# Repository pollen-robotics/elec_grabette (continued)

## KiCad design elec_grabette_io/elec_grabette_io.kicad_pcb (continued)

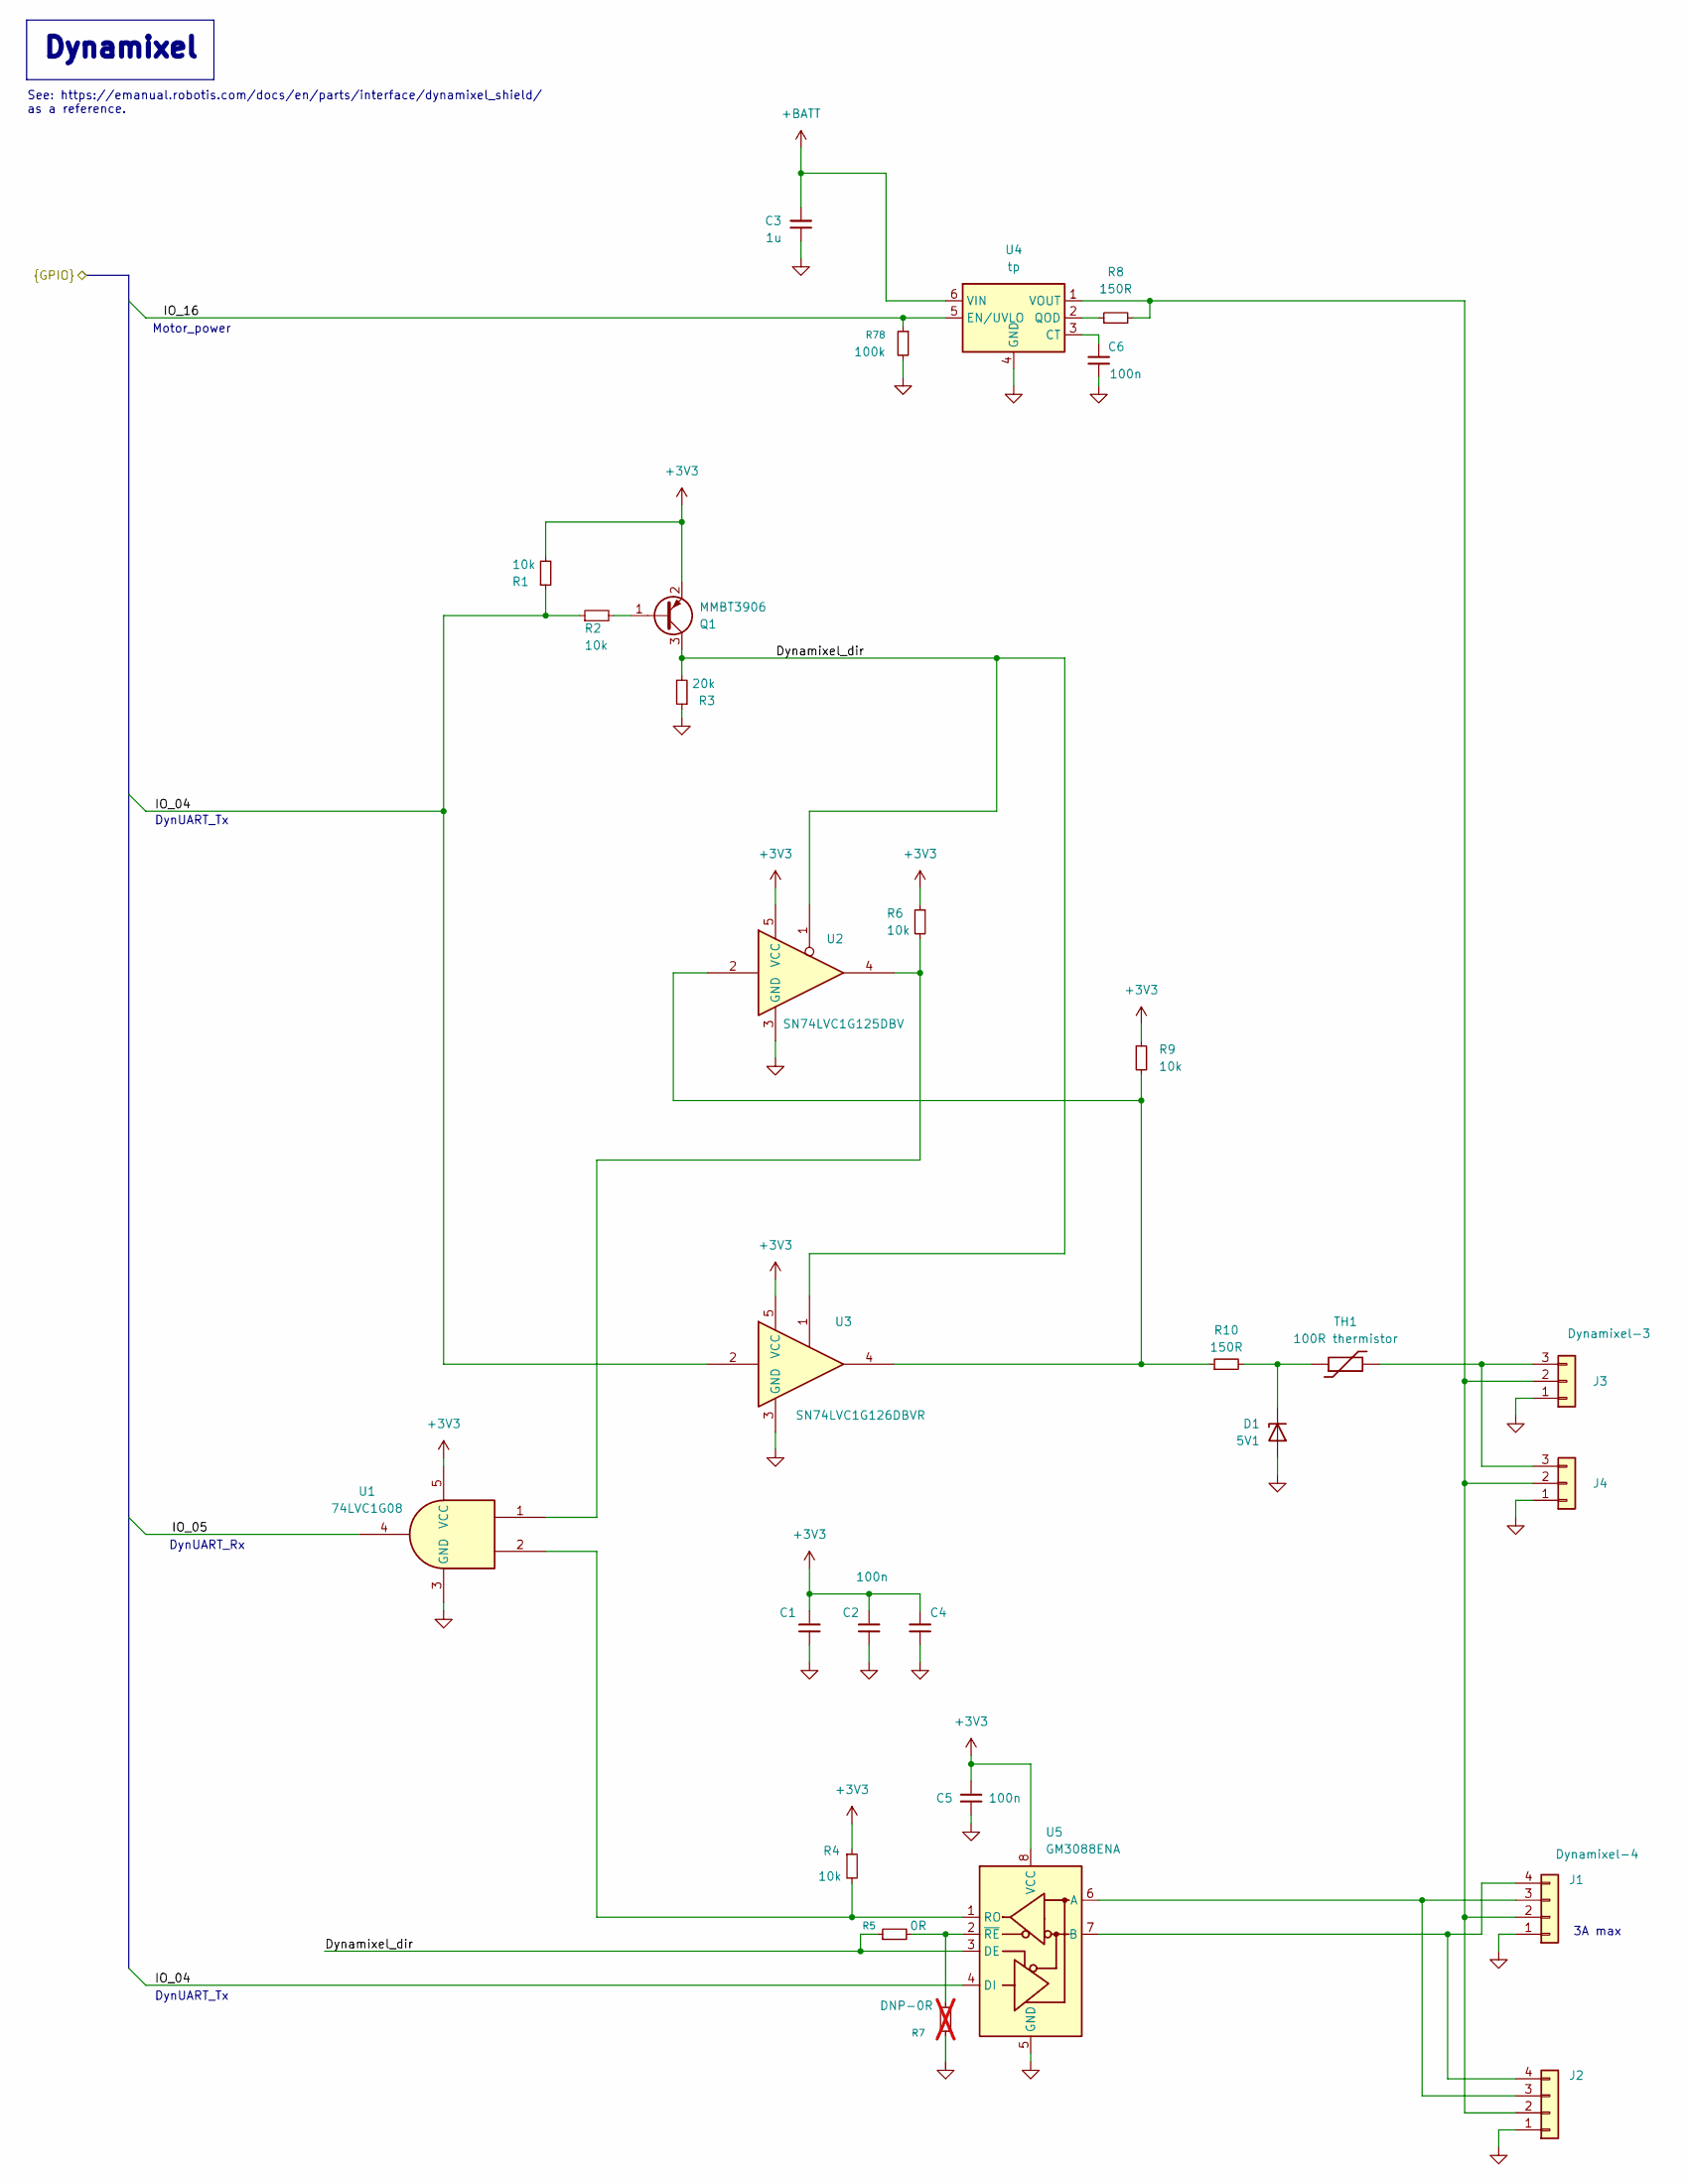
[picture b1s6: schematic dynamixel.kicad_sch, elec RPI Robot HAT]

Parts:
C1, C2, C4, C5, C6: 100n; C_0402_1005Metric; LCSC Part C307331
C3: 1u; C_0402_1005Metric; LCSC Part C52923
D1: 5V1; D_SOD-323; LCSC Part C151348
J1, J2: Dynamixel-4; JST_EH_B4B-EH-A_1x04_P2.50mm_Vertical; LCSC Part C160258
J3, J4: Dynamixel-3; JST_EH_B3B-EH-A_1x03_P2.50mm_Vertical; LCSC Part C160259
Q1: MMBT3906; SOT-23; LCSC Part C727128
R1, R2, R4, R6, R9: 10k; R_0402_1005Metric; LCSC Part C25744
R3: 20k; R_0402_1005Metric; LCSC Part C25765
R5: 0R; R_0402_1005Metric; LCSC Part C17168
R7: DNP-0R; R_0402_1005Metric; not fitted
R8, R10: 150R; R_0402_1005Metric; LCSC Part C2909321
R78: 100k; R_0402_1005Metric; LCSC Part C22369186
TH1: 100R thermistor; R_0603_1608Metric; LCSC Part C913703
U1: 74LVC1G08; SOT-23-5; LCSC Part C7666
U2: SN74LVC1G125DBV; SOT-23-5; LCSC Part C23654
U3: SN74LVC1G126DBVR; SOT-23-5; LCSC Part C7834
U4: tp; WSON-6-1EP_2x2mm_P0.65mm_EP1x1.6mm; LCSC Part C527679
U5: GM3088ENA; DFN-8-1EP_3x3mm_P0.65mm_EP1.2x2.15mm; LCSC Part C49423279

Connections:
+3V3: C1.2, C2.2, C4.2, C5.2, Q1.2 (E), R1.2, R4.1, R6.1, R9.1, U1.5 (VCC), U2.5 (VCC), U3.5 (VCC), U5.8 (VCC); also elsewhere on the board
+BATT: C3.2, U4.6 (VIN); also elsewhere on the board
/Audio/IO_04: R1.1, R2.1, U3.2, U5.4 (DI); also elsewhere on the board
/Audio/IO_05: U1.4; also elsewhere on the board
/Audio/IO_16: R78.1, U4.5 (EN/UVLO); also elsewhere on the board
/Dynamixel/Dynamixel_dir: Q1.3 (C), R3.2, R5.1, U2.1, U3.1, U5.3 (DE)
GND: C1.1, C2.1, C3.1, C4.1, C5.1, C6.1, D1.2 (A), J1.1, J2.1, J3.1, J4.1, R3.1, R7.1, R78.2, U1.3 (GND), U2.3 (GND), U3.3 (GND), U4.4 (GND), U4.7 (GND), U5.5 (GND); also elsewhere on the board
unnamed: D1.1 (K), R10.2, TH1.1
unnamed: J1.2, J2.2, J3.2, J4.2, R8.2, U4.1 (VOUT)
unnamed: J1.3, J2.3, U5.6 (A)
unnamed: J1.4, J2.4, U5.7 (B)
unnamed: J3.3, J4.3, TH1.2
unnamed: Q1.1 (B), R2.2
unnamed: R6.2, U1.1, U2.4
unnamed: R9.2, R10.1, U2.2, U3.4
unnamed: C6.2, U4.3 (CT)
unnamed: R8.1, U4.2 (QOD)
unnamed: R4.2, U1.2, U5.1 (RO)
unnamed: R5.2, R7.2, U5.2 (~RE)

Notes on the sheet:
DynUART_Tx
DynUART_Rx
See: https://emanual.robotis.com/docs/en/parts/interface/dynamixel_shield/ as a reference.
3A max
Motor_power
Dynamixel

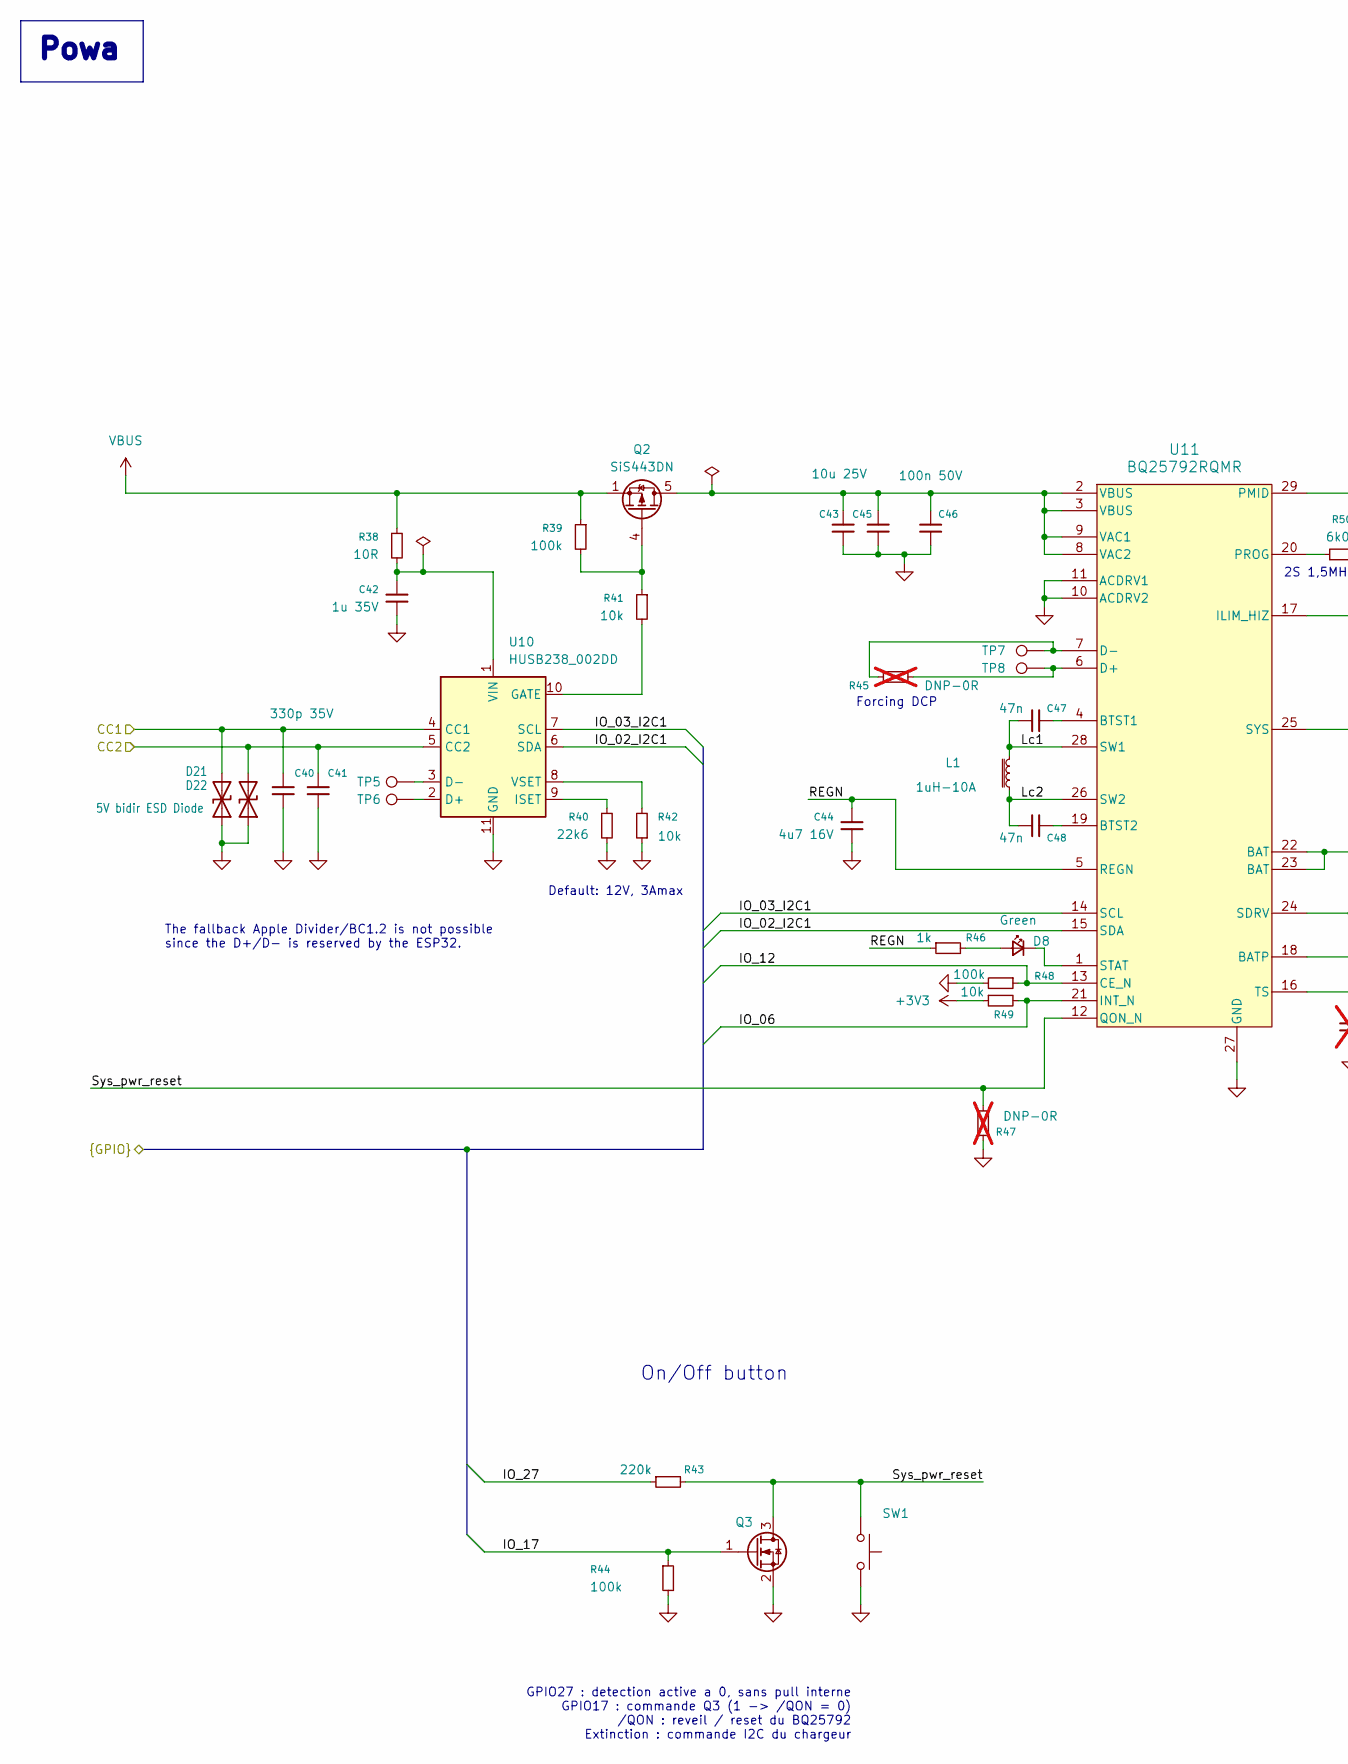
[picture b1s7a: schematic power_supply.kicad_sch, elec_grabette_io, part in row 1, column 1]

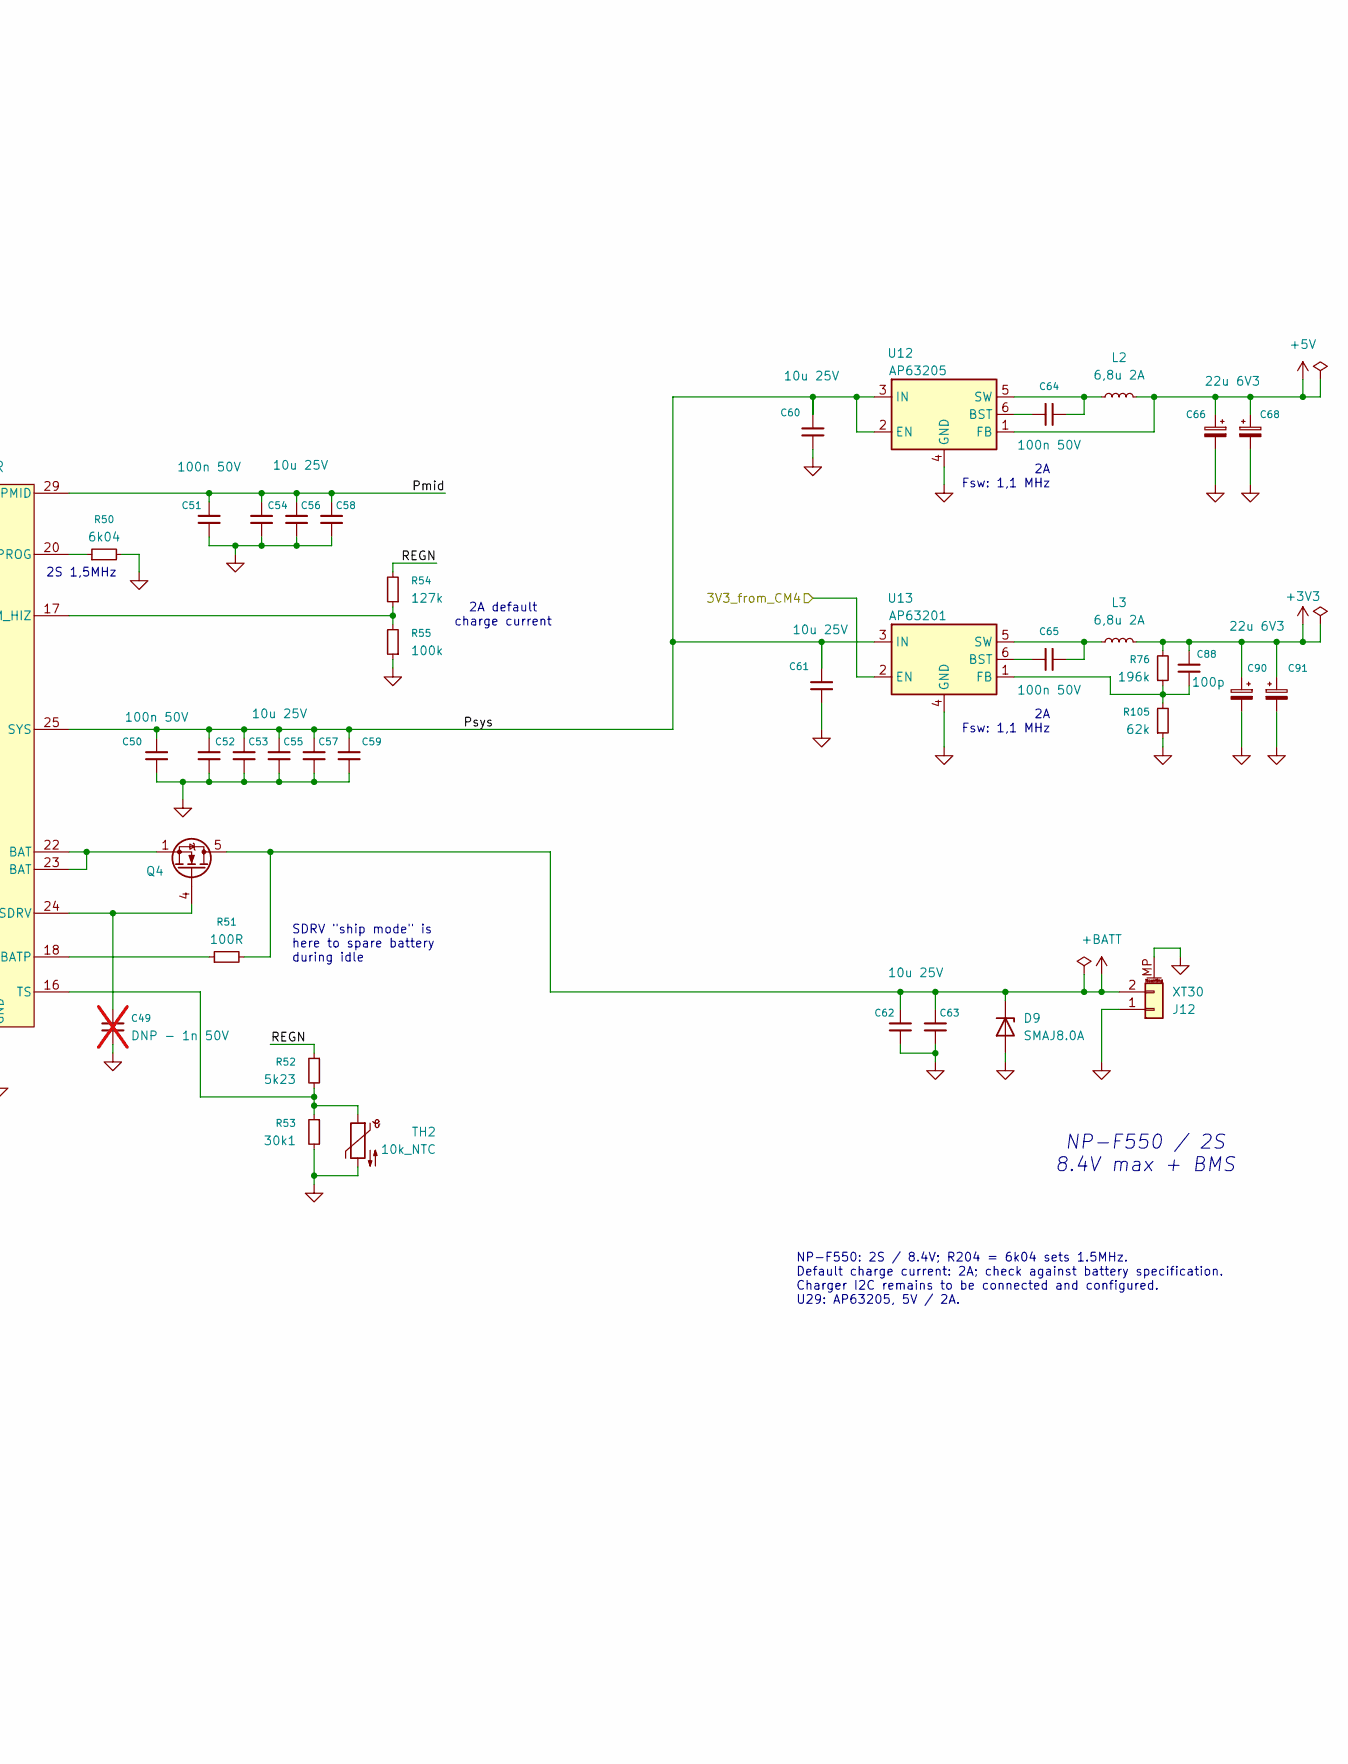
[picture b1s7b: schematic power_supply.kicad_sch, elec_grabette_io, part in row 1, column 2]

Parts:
C40, C41: 330p 35V; C_0402_1005Metric; LCSC Part C106206
C42: 1u 35V; C_0603_1608Metric; LCSC Part C15849
C43, C45, C52, C53, C54, C55, C56, C57, C58, C59, C60, C61, C62, C63: 10u 25V; C_0805_2012Metric; LCSC Part C15850
C44: 4u7 16V; C_0402_1005Metric; LCSC Part C23733
C46, C50, C51, C64, C65: 100n 50V; C_0402_1005Metric; LCSC Part C307331
C47, C48: 47n; C_0402_1005Metric; LCSC Part C880605
C49: DNP - 1n 50V; C_0402_1005Metric; not fitted
C66, C68, C90, C91: 22u 6V3; C_0603_1608Metric; LCSC Part C84419
C88: 100p; C_0402_1005Metric; LCSC Part C106200
D8: Green; LED_0603_1608Metric; LCSC Part C19171301
D9: SMAJ8.0A; D_SMA; LCSC Part C1972936
D21, D22: 5V bidir ESD Diode; D_0402_1005Metric; LCSC Part C48260
J12: XT30; AMASS_XT30PW-M_1x02_P2.50mm_Horizontal; LCSC Part C431092
L1: 1uH-10A; L_Sumida_CDMC6D28_7.25x6.5mm; LCSC Part C87572
L2, L3: 6,8u 2A; L_Bourns_SRN6045TA; LCSC Part C57254
Q2: SiS443DN; Vishay_PowerPAK_1212-8_Single; LCSC Part C41355039
Q3: BSS123; SOT-23; LCSC Part C7420338
Q4: CSD17575Q3; PQFN_3.3x3.3mm_-_PG-TDSON-8_FL; LCSC Part C529277
R38: 10R; R_0402_1005Metric; LCSC Part C138066
R39, R44, R48, R55: 100k; R_0402_1005Metric; LCSC Part C22369186
R40: 22k6; R_0402_1005Metric; LCSC Part C100316
R41, R42, R49: 10k; R_0402_1005Metric; LCSC Part C25744
R43: 220k; R_0402_1005Metric; LCSC Part C138030
R45, R47: DNP-0R; R_0402_1005Metric; not fitted
R46: 1k; R_0402_1005Metric; LCSC Part C105637
R50: 6k04; R_0402_1005Metric; Tolerance 1%; LCSC Part C97819
R51: 100R; R_0402_1005Metric; LCSC Part C106232
R52: 5k23; R_0402_1005Metric; LCSC Part C2933105
R53: 30k1; R_0402_1005Metric; LCSC Part C2998131
R54: 127k; R_0402_1005Metric; LCSC Part C5126094
R76: 196k; R_0402_1005Metric; LCSC Part C852585
R105: 62k; R_0402_1005Metric; LCSC Part C137950
SW1: SW_Push; KEY-TH_TC-6615-7-160G; LCSC Part C2845275
TH2: 10k_NTC; R_0603_1608Metric; LCSC Part C554013
TP5, TP6, TP7, TP8: TestPoint; TestPoint_Pad_D1.0mm
U10: HUSB238_002DD; WDFN-10-1EP_3x3mm_P0.5mm_EP1.8x2.5mm; LCSC Part C7471904
U11: BQ25792RQMR; RQM0029A-MFG; LCSC Part C2862876
U12: AP63205; TSOT-23-6; LCSC Part C2071056
U13: AP63201; TSOT-23-6; LCSC Part C2071044

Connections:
+3V3: C88.2, C90.1, C91.1, L3.1, R49.1, R76.2; also elsewhere on the board
+5V: C66.1, C68.1, L2.1, U12.1 (FB); also elsewhere on the board
+BATT: C62.1, C63.1, D9.1 (K), J12.2, Q4.5 (D), R51.2; also elsewhere on the board
/Audio/IO_02_I2C1: U10.6 (SDA), U11.15 (SDA); also elsewhere on the board
/Audio/IO_03_I2C1: U10.7 (SCL), U11.14 (SCL); also elsewhere on the board
/Audio/IO_06: R49.2, U11.21 (INT_N); also elsewhere on the board
/Audio/IO_12: R48.1, U11.13 (CE_N); also elsewhere on the board
/Audio/IO_17: Q3.1 (G), R44.1; also elsewhere on the board
/Audio/IO_27: R43.1; also elsewhere on the board
/CM4 GPIO/3V3_from_CM4: U13.2 (EN); also elsewhere on the board
/Power supply/CC1: C40.1, D21.2 (A2), U10.4 (CC1); also elsewhere on the board
/Power supply/CC2: C41.1, D22.2 (A2), U10.5 (CC2); also elsewhere on the board
/Power supply/Lc1: C47.1, L1.2, U11.28 (SW1)
/Power supply/Lc2: C48.1, L1.1, U11.26 (SW2)
/Power supply/Pmid: C51.2, C54.1, C56.1, C58.1, U11.29 (PMID)
/Power supply/Psys: C50.2, C52.1, C53.1, C55.1, C57.1, C59.1, C60.1, C61.1, U11.25 (SYS), U12.2 (EN), U12.3 (IN), U13.3 (IN)
/Power supply/REGN: C44.1, R46.1, R52.1, R54.2, U11.5 (REGN)
/Power supply/Sys_pwr_reset: Q3.3 (D), R43.2, R47.2, SW1.2, U11.12 (QON_N)
GND: C40.2, C41.2, C42.2, C43.2, C44.2, C45.2, C46.1, C49.2, C50.1, C51.1, C52.2, C53.2, C54.2, C55.2, C56.2, C57.2, C58.2, C59.2, C60.2, C61.2, C62.2, C63.2, C66.2, C68.2, C90.2, C91.2, D9.2 (A), D21.1 (A1), D22.1 (A1), J12.1, J12.MP (MountPin), Q3.2 (S), R40.2, R42.1, R44.2, R47.1, R48.2, R50.2, R53.2, R55.1, R105.1, SW1.1, TH2.2, U10.11 (GND), U11.10 (ACDRV2), U11.11 (ACDRV1), U11.27 (GND), U12.4 (GND), U13.4 (GND); also elsewhere on the board
unnamed: D8.2 (A), R46.2
unnamed: D8.1 (K), U11.1 (STAT)
unnamed: C43.1, C45.1, C46.2, Q2.5 (D), U11.2 (VBUS), U11.3 (VBUS), U11.8 (VAC2), U11.9 (VAC1)
unnamed: Q2.4 (G), R39.2, R41.1
unnamed: C49.1, Q4.4 (G), U11.24 (SDRV)
unnamed: Q4.1 (S), U11.22 (BAT), U11.23 (BAT)
unnamed: TP6.1 (1_1), U10.2 (D+)
unnamed: TP5.1 (1_1), U10.3 (D-)
unnamed: R41.2, U10.10 (GATE)
unnamed: R40.1, U10.9 (ISET)
unnamed: C42.1, R38.2, U10.1 (VIN)
unnamed: R42.2, U10.8 (VSET)
unnamed: R51.1, U11.18 (BATP)
unnamed: C47.2, U11.4 (BTST1)
unnamed: C48.2, U11.19 (BTST2)
unnamed: R45.1, TP8.1 (1_1), U11.6 (D+)
unnamed: R45.2, TP7.1 (1_1), U11.7 (D-)
unnamed: R54.1, R55.2, U11.17 (ILIM_HIZ)
unnamed: R50.1, U11.20 (PROG)
unnamed: R52.2, R53.1, TH2.1, U11.16 (TS)
unnamed: C64.1, U12.6 (BST)
unnamed: C64.2, L2.2, U12.5 (SW)
unnamed: C65.1, U13.6 (BST)
unnamed: C88.1, R76.1, R105.2, U13.1 (FB)
unnamed: C65.2, L3.2, U13.5 (SW)
VBUS: Q2.1 (S), Q2.2 (S), Q2.3 (S), R38.1, R39.1; also elsewhere on the board

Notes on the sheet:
The fallback Apple Divider/BC1.2 is not possible since the D+/D- is reserved by the ESP32.
Default: 12V, 3Amax
2A default charge current
NP-F550: 2S / 8.4V; R204 = 6k04 sets 1.5MHz. Default charge current: 2A; check against battery specification. Charger I2C remains to be connected and configured. U29: AP63205, 5V / 2A.
NP-F550 / 2S 8.4V max + BMS
On/Off button
Forcing DCP
SDRV "ship mode" is here to spare battery during idle
2A Fsw: 1,1 MHz
2S 1,5MHz
GPIO27 : detection active a 0, sans pull interne GPIO17 : commande Q3 (1 -> /QON = 0) /QON : reveil / reset du BQ25792 Extinction : commande I2C du chargeur
Powa

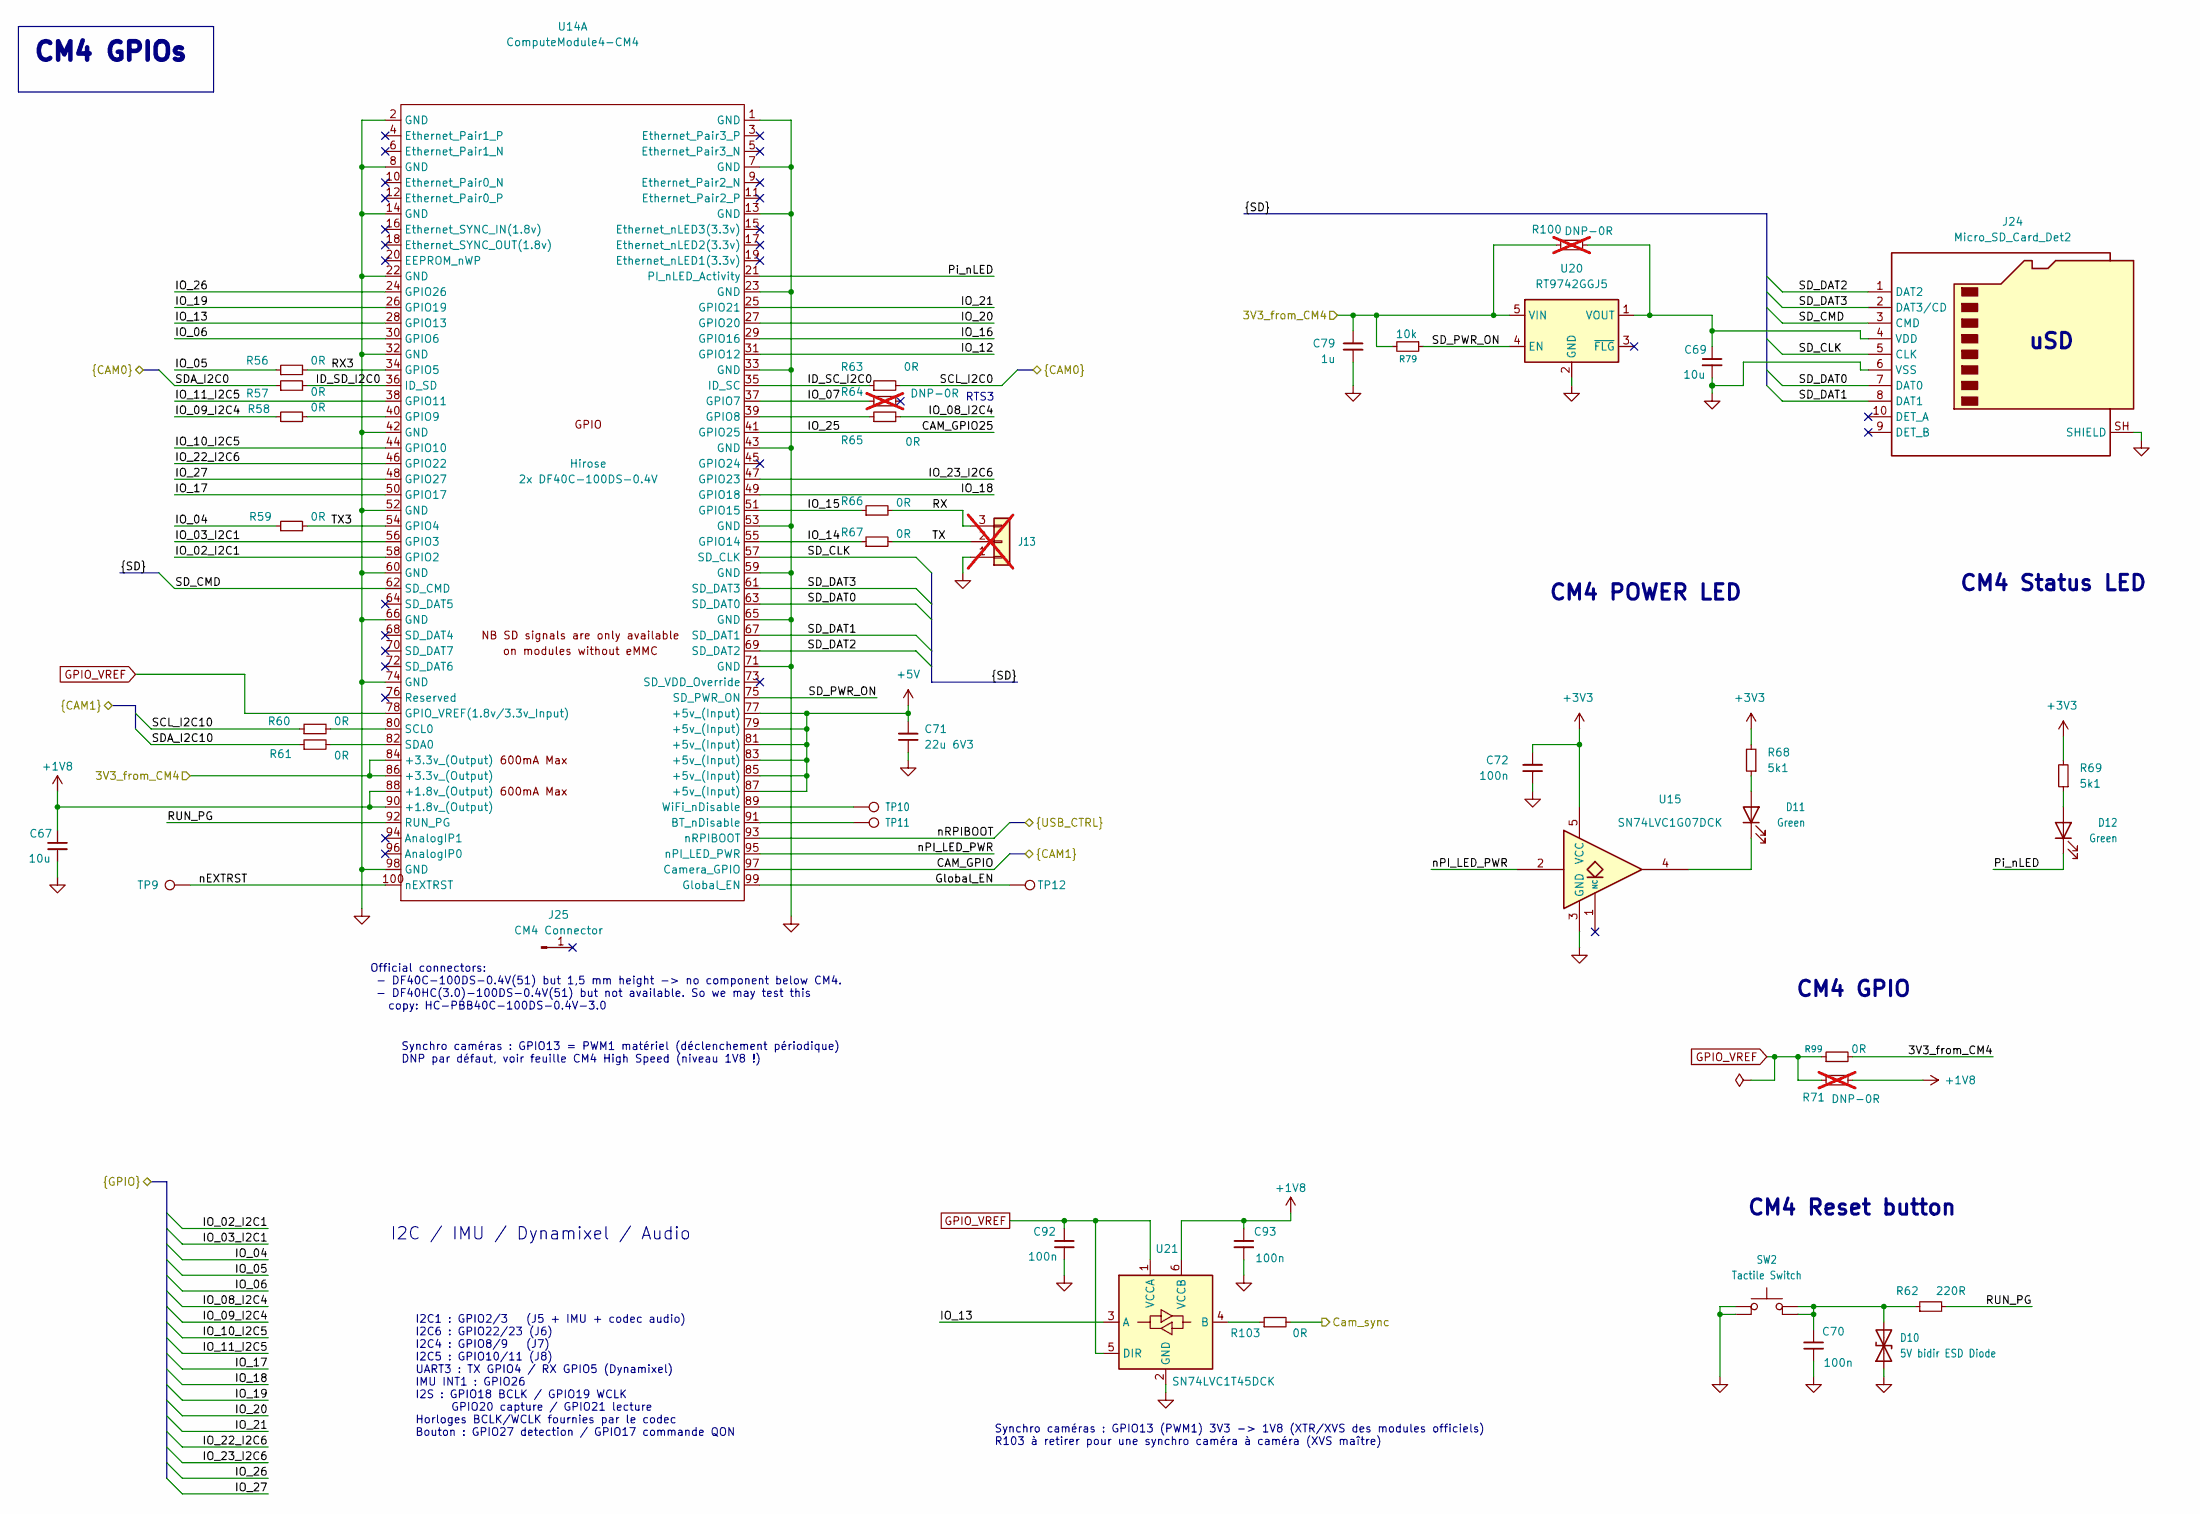
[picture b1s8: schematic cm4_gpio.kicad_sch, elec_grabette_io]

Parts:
C67, C69: 10u; C_0603_1608Metric; LCSC Part C1691
C70, C72, C92, C93: 100n; C_0402_1005Metric; Voltage Rating 16V; MPN CC0402KRX7R7BB104; LCSC Part C307331
C71: 22u 6V3; C_0603_1608Metric; Voltage Rating 25V; MPN CC0805MKX5R8BB226; LCSC Part C84419
C79: 1u; C_0402_1005Metric; LCSC Part C52923
D10: 5V bidir ESD Diode; D_0402_1005Metric; LCSC Part C48260
D11, D12: Green; LED_0603_1608Metric; MPN 19-217/G7C-AN1P2/3T; LCSC Part C19171301
J13: DNP-Header 1x3; PinHeader_1x03_P1.27mm_Vertical; MPN P125-1103A1BS116A; not fitted
J24: Micro_SD_Card_Det2; SIM-SMD_8P-1040310811; LCSC Part C585350
J25: CM4 Connector; position_only; LCSC Part C597931
R56, R57, R58, R59, R60, R61, R63, R65, R66, R67, R103: 0R; R_0402_1005Metric; Power Rating 5%; MPN RC0402JR-070RL; LCSC Part C17168
R62: 220R; R_0402_1005Metric; LCSC Part C112291
R64, R100: DNP-0R; R_0402_1005Metric; Power Rating 5%; MPN RC0402JR-070RL; not fitted
R68, R69: 5k1; R_0402_1005Metric; Power Rating 5%; MPN RC0402JR-075K1L; LCSC Part C25905
R71: DNP-0R; R_0402_1005Metric; Power Rating 5%; MPN RC0402JR-070RL; LCSC Part C17168; not fitted
R79: 10k; R_0402_1005Metric; LCSC Part C25744
R99: 0R; R_0402_1005Metric; LCSC Part C17168
SW2: Tactile Switch; KEY-SMD_4P-L4.2-W3.2-P2.20-LS4.6; MPN SKRPADE010; LCSC Part C127488
TP9, TP12: GLOBAL_EN; TestPoint_Pad_D1.0mm
TP10, TP11: TestPoint; TestPoint_Pad_D1.0mm; Part Type Test Point
U14: ComputeModule4-CM4; Raspberry-Pi-4-Compute-Module
U15: SN74LVC1G07DCK; SOT-353_SC-70-5; MPN SN74LVC1G07DCK; LCSC Part C55509819
U20: RT9742GGJ5; TSOT-23-5; LCSC Part C250547
U21: SN74LVC1T45DCK; SOT-363_SC-70-6; MPN SN74LVC1T45DCKR; LCSC Part C9382

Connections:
+1V8: C67.1, C93.1, R71.2, U14.88 (+1.8v_(Output)), U14.90 (+1.8v_(Output)), U21.6 (VCCB)
+3V3: C72.1, R68.2, R69.2, U15.5 (VCC); also elsewhere on the board
+5V: C71.1, U14.77 (+5v_(Input)), U14.79 (+5v_(Input)), U14.81 (+5v_(Input)), U14.83 (+5v_(Input)), U14.85 (+5v_(Input)), U14.87 (+5v_(Input)); also elsewhere on the board
/Audio/ID_SC_I2C0: R63.1, U14.35 (ID_SC)
/Audio/ID_SD_I2C0: R57.2, U14.36 (ID_SD)
/Audio/IO_02_I2C1: U14.58 (GPIO2); also elsewhere on the board
/Audio/IO_03_I2C1: U14.56 (GPIO3); also elsewhere on the board
/Audio/IO_04: R59.1; also elsewhere on the board
/Audio/IO_05: R56.1; also elsewhere on the board
/Audio/IO_06: U14.30 (GPIO6); also elsewhere on the board
/Audio/IO_07: R64.1, U14.37 (GPIO7)
/Audio/IO_08_I2C4: R65.2; also elsewhere on the board
/Audio/IO_09_I2C4: R58.1; also elsewhere on the board
/Audio/IO_10_I2C5: U14.44 (GPIO10); also elsewhere on the board
/Audio/IO_11_I2C5: U14.38 (GPIO11); also elsewhere on the board
/Audio/IO_12: U14.31 (GPIO12); also elsewhere on the board
/Audio/IO_13: U14.28 (GPIO13), U21.3 (A)
/Audio/IO_14: R67.1, U14.55 (GPIO14)
/Audio/IO_15: R66.1, U14.51 (GPIO15)
/Audio/IO_16: U14.29 (GPIO16); also elsewhere on the board
/Audio/IO_17: U14.50 (GPIO17); also elsewhere on the board
/Audio/IO_18: U14.49 (GPIO18); also elsewhere on the board
/Audio/IO_19: U14.26 (GPIO19); also elsewhere on the board
/Audio/IO_20: U14.27 (GPIO20); also elsewhere on the board
/Audio/IO_21: U14.25 (GPIO21); also elsewhere on the board
/Audio/IO_22_I2C6: U14.46 (GPIO22); also elsewhere on the board
/Audio/IO_23_I2C6: U14.47 (GPIO23); also elsewhere on the board
/Audio/IO_25: U14.41 (GPIO25); also elsewhere on the board
/Audio/IO_26: U14.24 (GPIO26); also elsewhere on the board
/Audio/IO_27: U14.48 (GPIO27); also elsewhere on the board
/CM4 GPIO/3V3_from_CM4: C79.2, R79.2, R99.2, R100.1, U14.84 (+3.3v_(Output)), U14.86 (+3.3v_(Output)), U20.5 (VIN); also elsewhere on the board
/CM4 GPIO/CAM_GPIO: U14.97 (Camera_GPIO); also elsewhere on the board
/CM4 GPIO/Cam_sync: R103.2; also elsewhere on the board
/CM4 GPIO/Global_EN: TP12.1 (1_1), U14.99 (Global_EN)
/CM4 GPIO/Pi_nLED: D12.1 (K), U14.21 (PI_nLED_Activity)
/CM4 GPIO/RUN_PG: R62.2, U14.92 (RUN_PG)
/CM4 GPIO/RX: J13.3, R66.2
/CM4 GPIO/RX3: R56.2, U14.34 (GPIO5)
/CM4 GPIO/SCL_I2C0: R63.2; also elsewhere on the board
/CM4 GPIO/SCL_I2C10: R60.1; also elsewhere on the board
/CM4 GPIO/SDA_I2C0: R57.1; also elsewhere on the board
/CM4 GPIO/SDA_I2C10: R61.1; also elsewhere on the board
/CM4 GPIO/SD_CLK: J24.5 (CLK), U14.57 (SD_CLK)
/CM4 GPIO/SD_CMD: J24.3 (CMD), U14.62 (SD_CMD)
/CM4 GPIO/SD_DAT0: J24.7 (DAT0), U14.63 (SD_DAT0)
/CM4 GPIO/SD_DAT1: J24.8 (DAT1), U14.67 (SD_DAT1)
/CM4 GPIO/SD_DAT2: J24.1 (DAT2), U14.69 (SD_DAT2)
/CM4 GPIO/SD_DAT3: J24.2 (DAT3/CD), U14.61 (SD_DAT3)
/CM4 GPIO/SD_PWR_ON: R79.1, U14.75 (SD_PWR_ON), U20.4 (EN)
/CM4 GPIO/TX: J13.2, R67.2
/CM4 GPIO/TX3: R59.2, U14.54 (GPIO4)
/CM4 GPIO/nEXTRST: TP9.1 (1_1), U14.100 (nEXTRST)
/CM4 GPIO/nPI_LED_PWR: U14.95 (nPI_LED_PWR), U15.2
/CM4 GPIO/nRPIBOOT: U14.93 (nRPIBOOT); also elsewhere on the board
GND: C67.2, C69.2, C70.2, C71.2, C72.2, C79.1, C92.2, C93.2, D10.1 (A1), J13.1, J24.6 (VSS), J24.SH (SHIELD), SW2.1, SW2.2, U14.1 (GND), U14.2 (GND), U14.7 (GND), U14.8 (GND), U14.13 (GND), U14.14 (GND), U14.22 (GND), U14.23 (GND), U14.32 (GND), U14.33 (GND), U14.42 (GND), U14.43 (GND), U14.52 (GND), U14.53 (GND), U14.59 (GND), U14.60 (GND), U14.65 (GND), U14.66 (GND), U14.71 (GND), U14.74 (GND), U14.98 (GND), U15.3 (GND), U20.2 (GND), U21.2 (GND); also elsewhere on the board
GPIO_VREF: C92.1, R71.1, R99.1, U14.78 (GPIO_VREF(1.8v/3.3v_Input)), U21.1 (VCCA), U21.5 (DIR); also elsewhere on the board
unnamed: C70.1, D10.2 (A2), R62.1, SW2.3, SW2.4
unnamed: D11.2 (A), R68.1
unnamed: D11.1 (K), U15.4
unnamed: D12.2 (A), R69.1
unnamed: C69.1, J24.4 (VDD), R100.2, U20.1 (VOUT)
unnamed: TP11.1 (1_1), U14.91 (BT_nDisable)
unnamed: R65.1, U14.39 (GPIO8)
unnamed: R58.2, U14.40 (GPIO9)
unnamed: R60.2, U14.80 (SCL0)
unnamed: R61.2, U14.82 (SDA0)
unnamed: TP10.1 (1_1), U14.89 (WiFi_nDisable)
unnamed: R103.1, U21.4 (B)

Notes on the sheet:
Official connectors: - DF40C-100DS-0.4V(51) but 1,5 mm height -> no component below CM4. - DF40HC(3.0)-100DS-0.4V(51) but not available. So we may test this copy: HC-PBB40C-100DS-0.4V-3.0
CM4 Reset button
Synchro caméras : GPIO13 = PWM1 matériel (déclenchement périodique) DNP par défaut, voir feuille CM4 High Speed (niveau 1V8 !)
CM4 GPIO
uSD
Synchro caméras : GPIO13 (PWM1) 3V3 -> 1V8 (XTR/XVS des modules officiels) R103 à retirer pour une synchro caméra à caméra (XVS maître)
I2C1 : GPIO2/3 (J5 + IMU + codec audio) I2C6 : GPIO22/23 (J6) I2C4 : GPIO8/9 (J7) I2C5 : GPIO10/11 (J8) UART3 : TX GPIO4 / RX GPIO5 (Dynamixel) IMU INT1 : GPIO26 I2S : GPIO18 BCLK / GPIO19 WCLK GPIO20 capture / GPIO21 lecture Horloges BCLK/WCLK fournies par le codec Bouton : GPIO27 detection / GPIO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
RTS3
I2C / IMU / Dynamixel / Audio
CM4 POWER LED
CM4 Status LED
CM4 GPIOs
